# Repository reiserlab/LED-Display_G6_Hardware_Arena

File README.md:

## LED Display G6 Hardware Arena

This repository is part of <https://reiserlab.github.io/Modular-LED-Display/>. It contains the KiCad design files and production files for the Generation 6 arena hardware.

### Overview

The arena PCB serves as the backplane for a Generation 6 Modular LED Display. It supports up to 10 LED panel boards arranged in a circle to form a cylindrical structure. The board is driven by a Teensy 4.1 MCU and receives updates via Ethernet.

The first large production run was version 1.1.7, ordered on 2026-04-28.

## Development and License

The original design was created by Will Dickson of [IORodeo](https://iorodeo.com) for the [Reiser Lab](https://janelia.org/lab/reiser-lab) at [Janelia | HHMI](https://www.janelia.org/). See `LICENSE`.

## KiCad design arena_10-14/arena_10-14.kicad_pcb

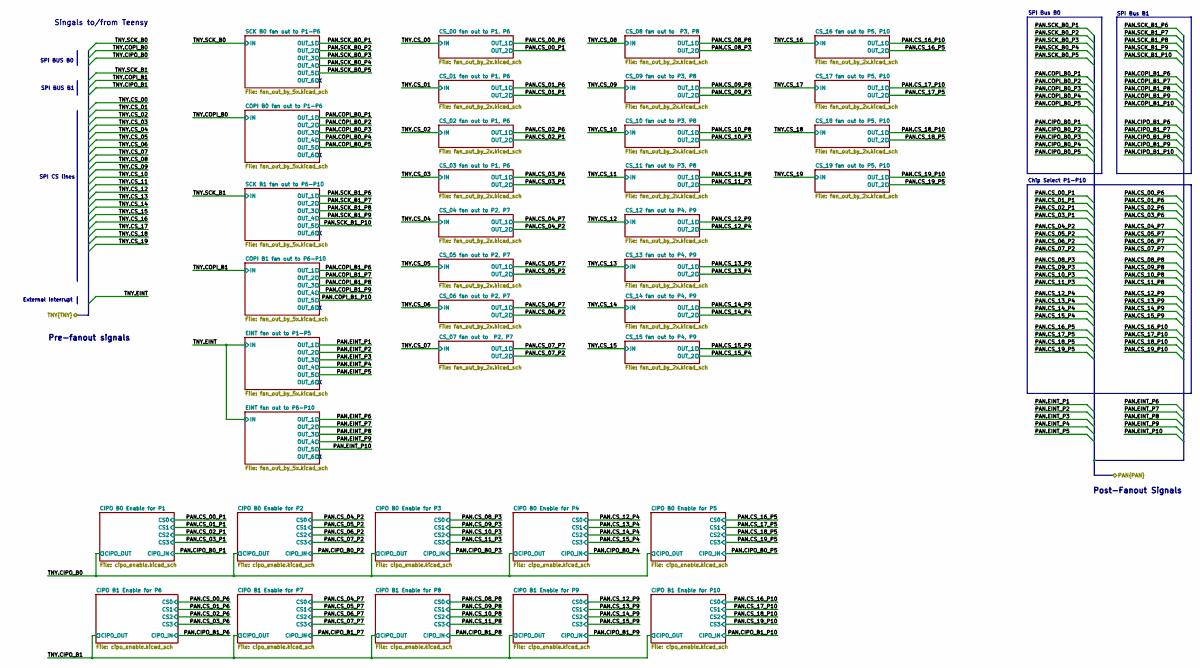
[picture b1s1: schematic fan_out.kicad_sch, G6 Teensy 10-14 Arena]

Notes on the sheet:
Chip Select P1-P10
Pre-fanout signals
SPI BUS B0
SPI BUS B1
External Interrupt
Post-Fanout Signals
SPI Bus B0
Singals to/from Teensy
SPI Bus B1
SPI CS lines

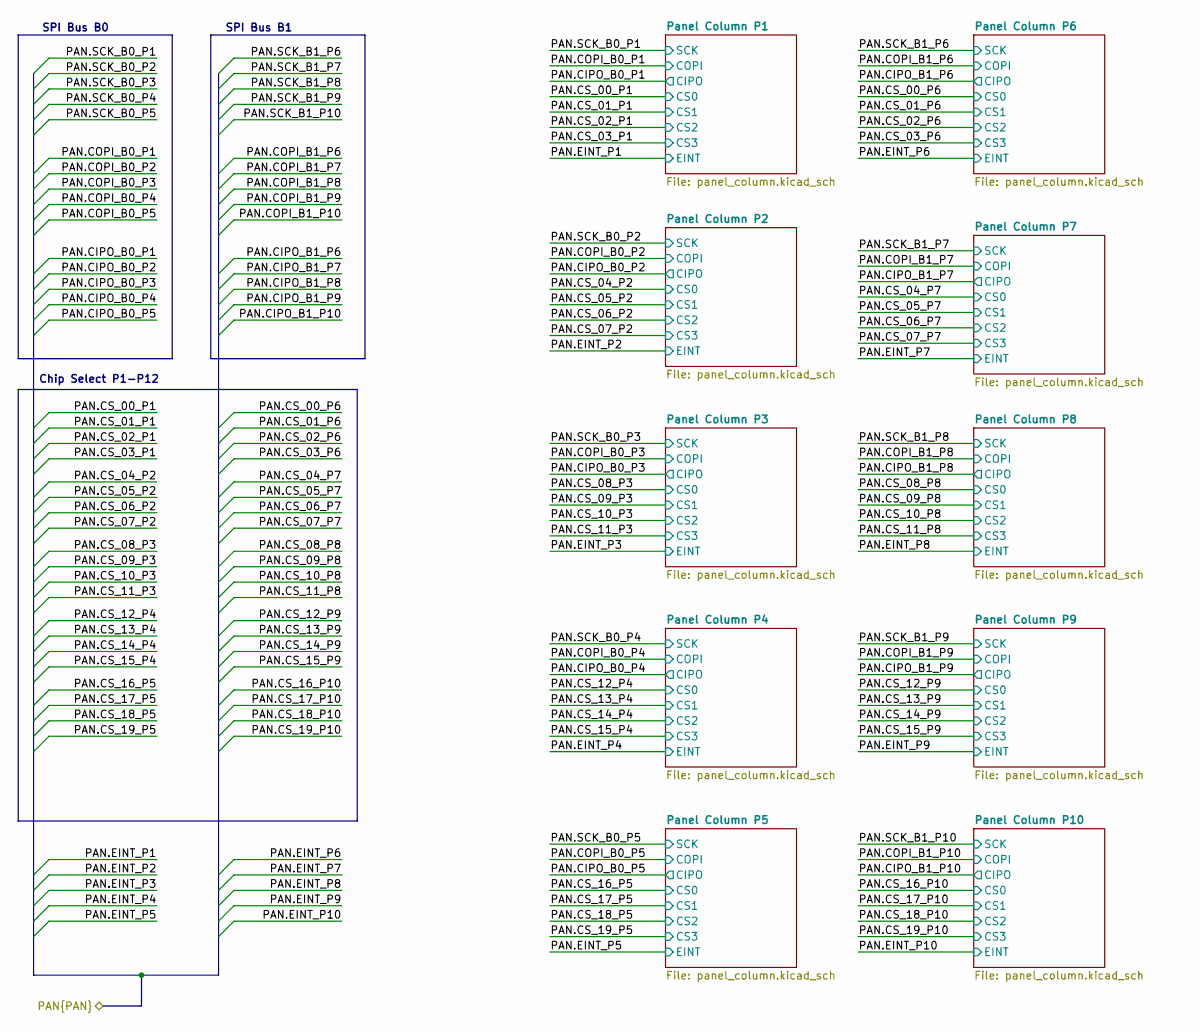
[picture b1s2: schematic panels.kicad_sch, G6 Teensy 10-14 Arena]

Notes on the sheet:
SPI Bus B1
Chip Select P1-P12
SPI Bus B0

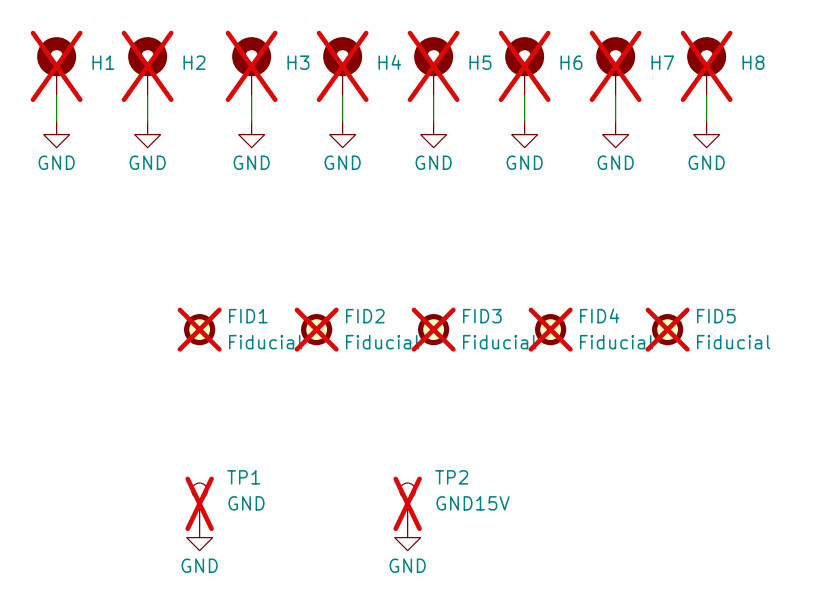
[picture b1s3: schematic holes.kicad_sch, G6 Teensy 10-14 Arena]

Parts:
FID1, FID2, FID3, FID4, FID5: Fiducial; Fiducial_0.5mm_Mask1mm; not fitted
H1, H2, H3, H4, H8: MountingHole_Pad; MountingHole_6.5mm_Pad_Via; not fitted
H5, H6, H7: MountingHole_Pad; MountingHole_6.5mm_Pad_TopBottom; not fitted
TP1: GND; TestPoint_Pad_D1.5mm; not fitted
TP2: GND15V; TestPoint_Pad_D1.5mm; not fitted

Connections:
GND: H1.1 (1_1), H2.1 (1_1), H3.1 (1_1), H4.1 (1_1), H5.1 (1_1), H6.1 (1_1), H7.1 (1_1), H8.1 (1_1), TP1.1 (1_1), TP2.1 (1_1); also elsewhere on the board

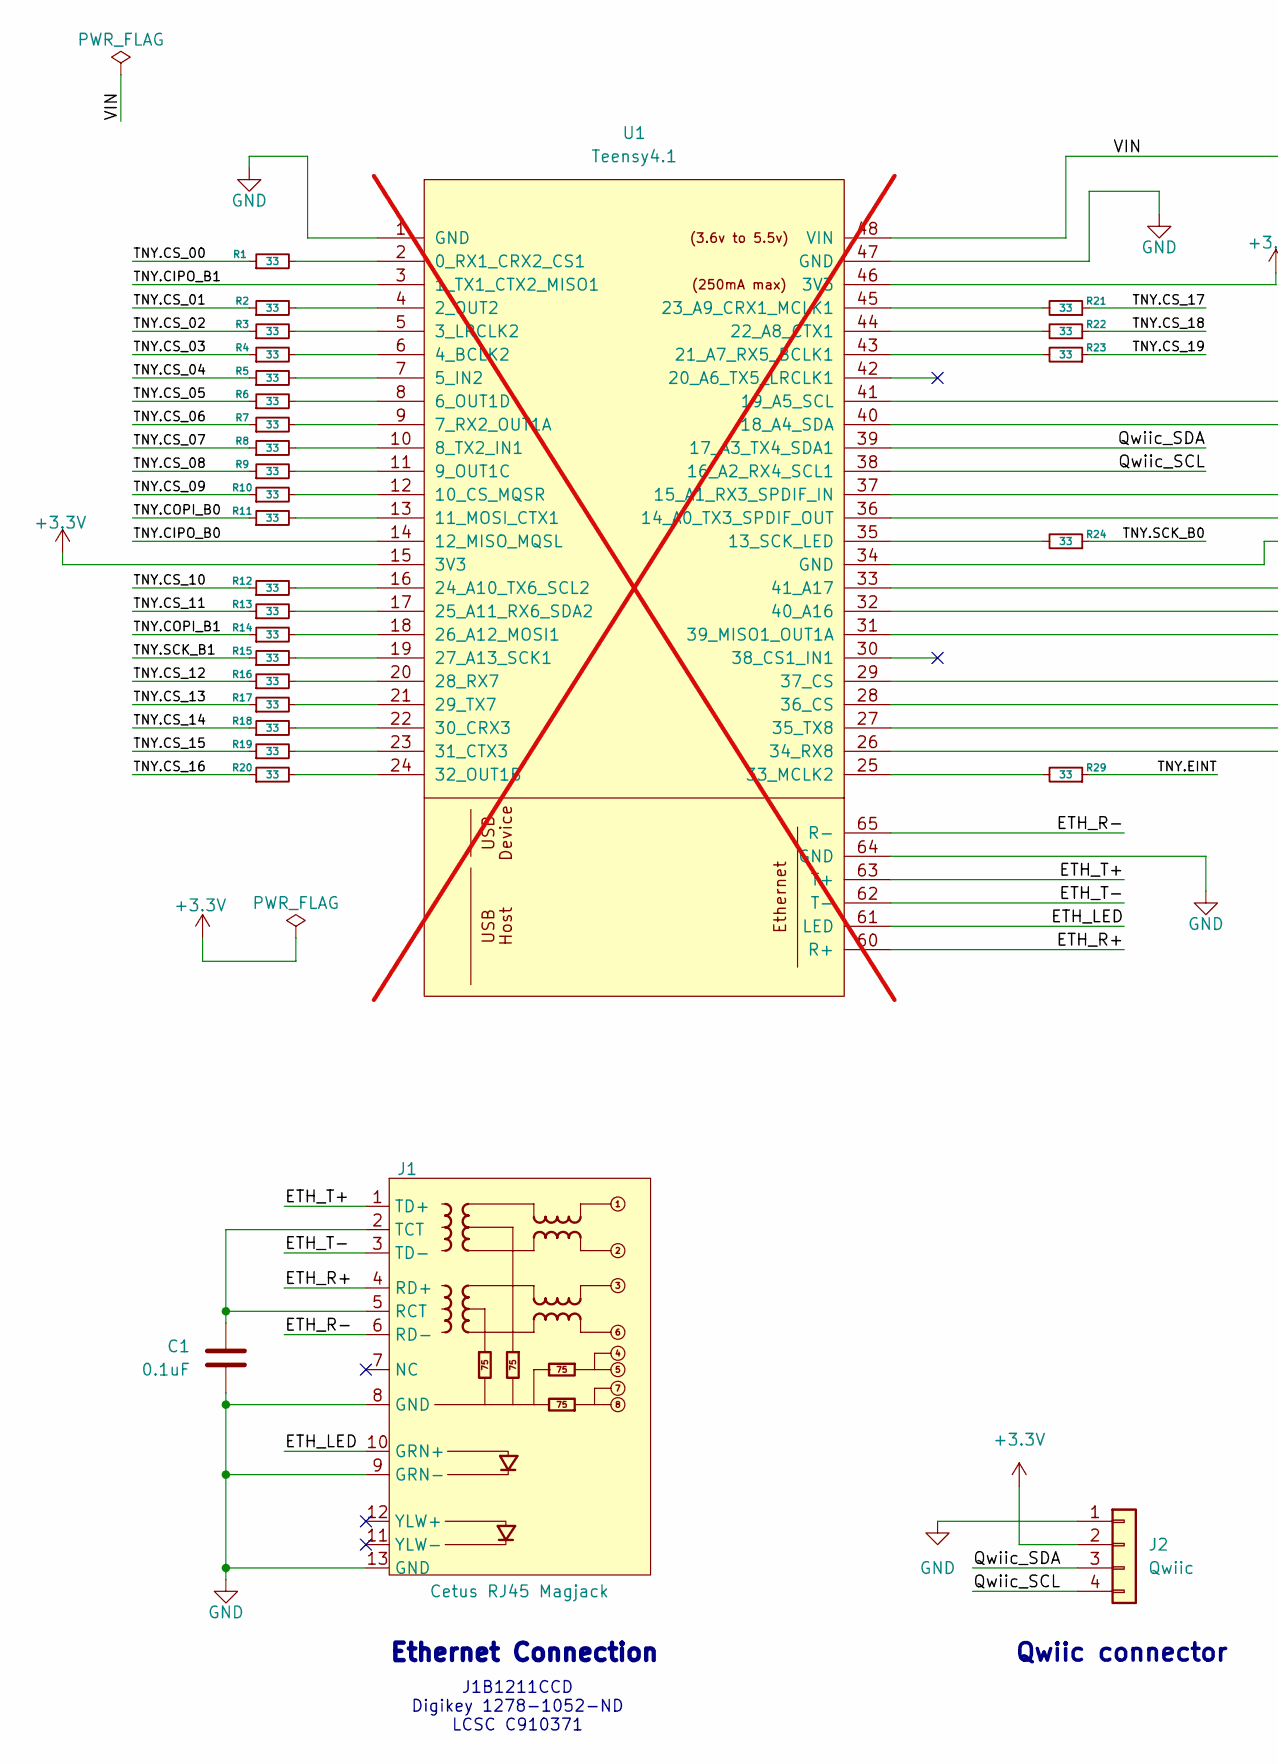
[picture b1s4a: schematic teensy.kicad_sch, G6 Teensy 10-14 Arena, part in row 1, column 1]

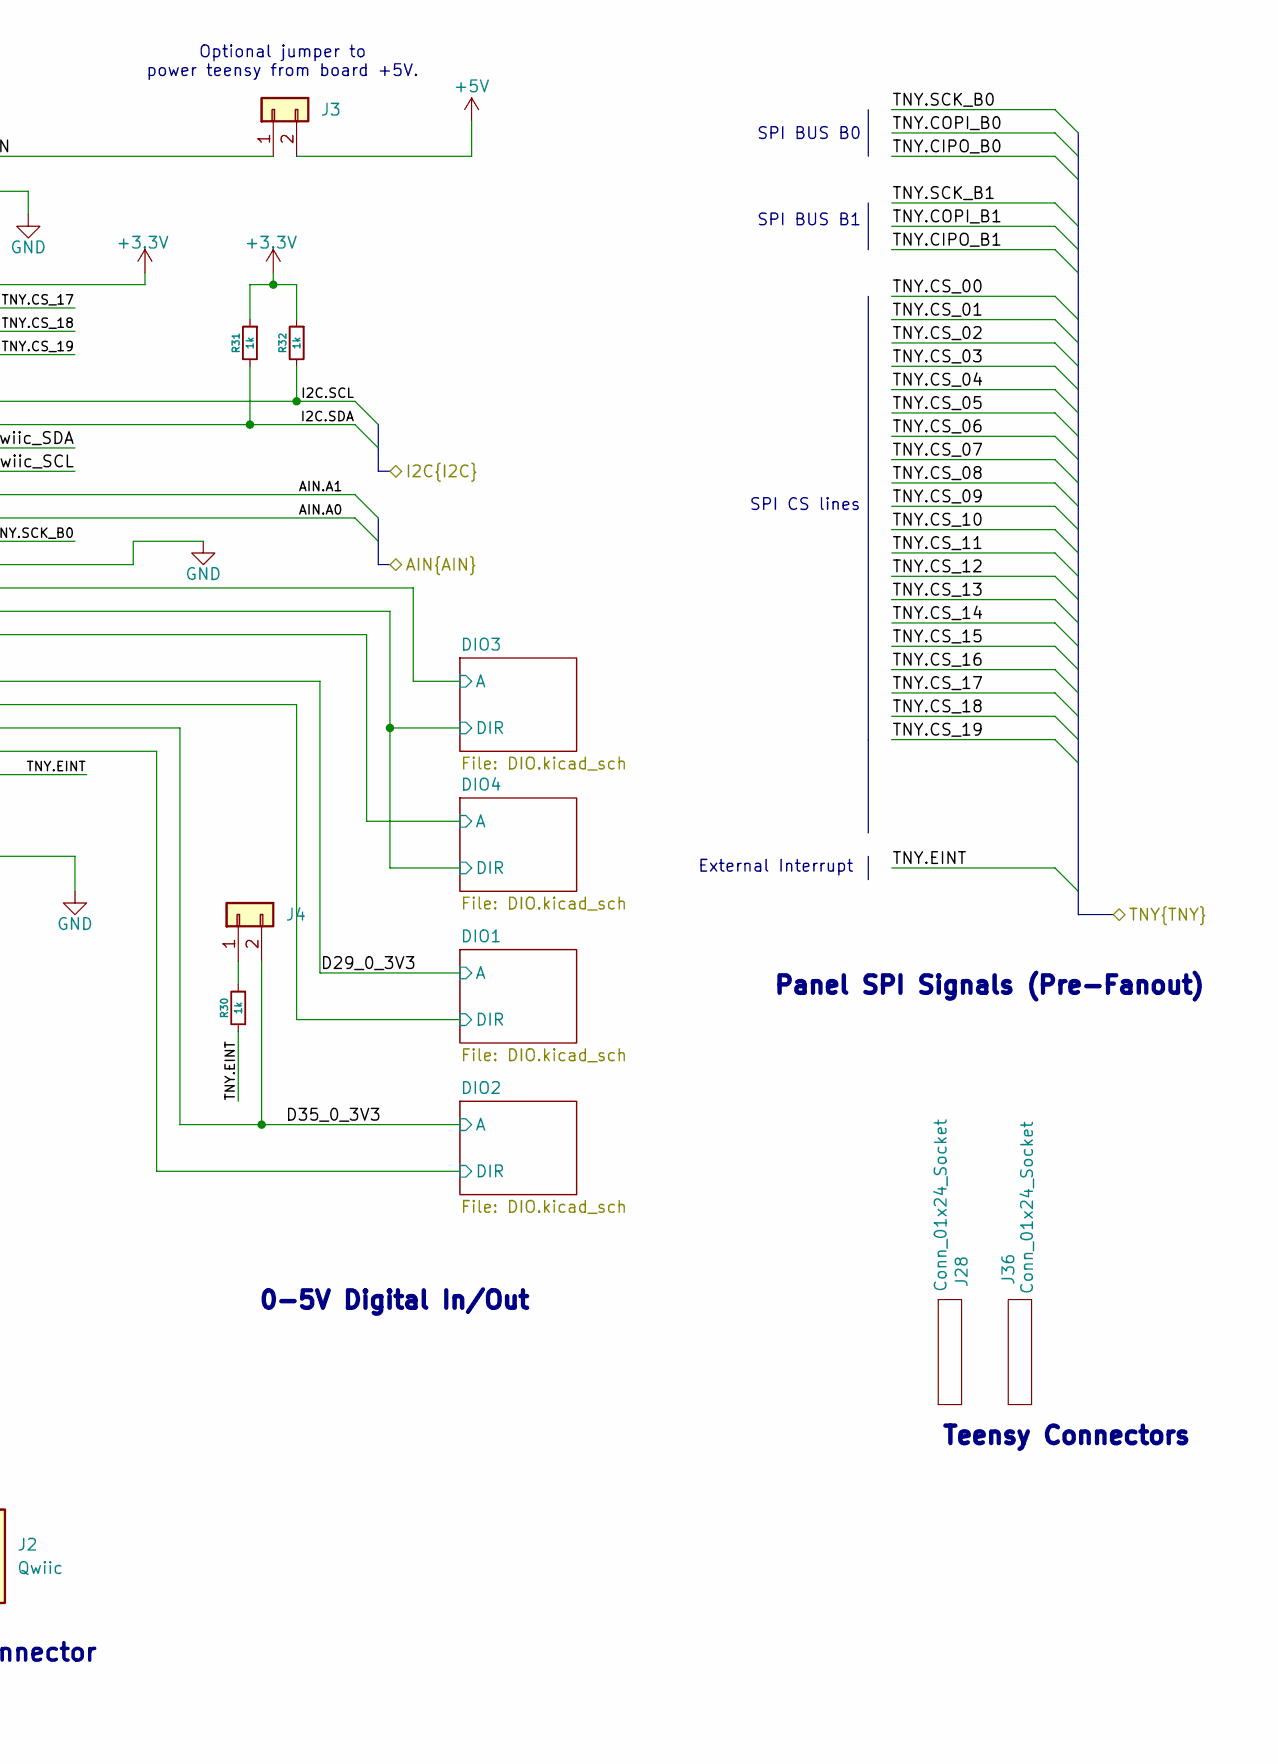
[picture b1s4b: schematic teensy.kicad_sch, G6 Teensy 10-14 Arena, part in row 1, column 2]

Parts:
C1: 0.1uF; C_0402_1005Metric; LCSC Part # C1525
J1: Cetus RJ45 Magjack; RJ45_Cetus_J1B1211CCD_Horizontal; LCSC Part # C910371
J2: Qwiic; JST_SH_SM04B-SRSS-TB_1x04-1MP_P1.00mm_Horizontal; MPN SM04B-SRSS-TB; DigiKey PN 455-SM04B-SRSS-TBTR-ND
J3, J4: Conn_01x02; PinHeader_1x02_P2.54mm_Vertical; LCSC Part # C124375
J28, J36: Conn_01x24_Socket; PinSocket_1x24_P2.54mm_Vertical; LCSC Part # C41376163
R1, R2, R3, R4, R5, R6, R7, R8, R9, R10, R11, R12, R13, R14, R15, R16, R17, R18, R19, R20, R21, R22, R23, R24, R29: 33; R_0402_1005Metric; LCSC Part # C25105
R30, R31, R32: 1k; R_0402_1005Metric; LCSC Part # C11702
U1: Teensy4.1; Teensy41_ethernet_only; not fitted

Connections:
+3.3V: J2.2, R31.1, R32.1, U1.15 (3V3), U1.46 (3V3); also elsewhere on the board
+5V: J3.2; also elsewhere on the board
/Analog IO/AIN.A0: U1.36 (14_A0_TX3_SPDIF_OUT); also elsewhere on the board
/Analog IO/AIN.A1: U1.37 (15_A1_RX3_SPDIF_IN); also elsewhere on the board
/Analog IO/I2C.SCL: R32.2, U1.41 (19_A5_SCL); also elsewhere on the board
/Analog IO/I2C.SDA: R31.2, U1.40 (18_A4_SDA); also elsewhere on the board
/Fan Out/TNY.CIPO_B0: U1.14 (12_MISO_MQSL); also elsewhere on the board
/Fan Out/TNY.CIPO_B1: U1.3 (1_TX1_CTX2_MISO1); also elsewhere on the board
/Fan Out/TNY.COPI_B0: R11.1; also elsewhere on the board
/Fan Out/TNY.COPI_B1: R14.1; also elsewhere on the board
/Fan Out/TNY.CS_00: R1.1; also elsewhere on the board
/Fan Out/TNY.CS_01: R2.1; also elsewhere on the board
/Fan Out/TNY.CS_02: R3.1; also elsewhere on the board
/Fan Out/TNY.CS_03: R4.1; also elsewhere on the board
/Fan Out/TNY.CS_04: R5.1; also elsewhere on the board
/Fan Out/TNY.CS_05: R6.1; also elsewhere on the board
/Fan Out/TNY.CS_06: R7.1; also elsewhere on the board
/Fan Out/TNY.CS_07: R8.1; also elsewhere on the board
/Fan Out/TNY.CS_08: R9.1; also elsewhere on the board
/Fan Out/TNY.CS_09: R10.1; also elsewhere on the board
/Fan Out/TNY.CS_10: R12.1; also elsewhere on the board
/Fan Out/TNY.CS_11: R13.1; also elsewhere on the board
/Fan Out/TNY.CS_12: R16.1; also elsewhere on the board
/Fan Out/TNY.CS_13: R17.1; also elsewhere on the board
/Fan Out/TNY.CS_14: R18.1; also elsewhere on the board
/Fan Out/TNY.CS_15: R19.1; also elsewhere on the board
/Fan Out/TNY.CS_16: R20.1; also elsewhere on the board
/Fan Out/TNY.CS_17: R21.1; also elsewhere on the board
/Fan Out/TNY.CS_18: R22.1; also elsewhere on the board
/Fan Out/TNY.CS_19: R23.1; also elsewhere on the board
/Fan Out/TNY.EINT: R29.1, R30.2; also elsewhere on the board
/Fan Out/TNY.SCK_B0: R24.1; also elsewhere on the board
/Fan Out/TNY.SCK_B1: R15.1; also elsewhere on the board
/Teensy/D29_0_3V3: U1.29 (37_CS); also elsewhere on the board
/Teensy/D35_0_3V3: J4.2, U1.27 (35_TX8); also elsewhere on the board
/Teensy/DIO1/DIR: U1.28 (36_CS); also elsewhere on the board
/Teensy/DIO2/DIR: U1.26 (34_RX8); also elsewhere on the board
/Teensy/DIO3/A: U1.33 (41_A17); also elsewhere on the board
/Teensy/DIO3/DIR: U1.32 (40_A16); also elsewhere on the board
/Teensy/DIO4/A: U1.31 (39_MISO1_OUT1A); also elsewhere on the board
/Teensy/ETH_LED: J1.10 (GRN+), U1.61 (LED)
/Teensy/ETH_R+: J1.4 (RD+), U1.60 (R+)
/Teensy/ETH_R-: J1.6 (RD-), U1.65 (R-)
/Teensy/ETH_T+: J1.1 (TD+), U1.63 (T+)
/Teensy/ETH_T-: J1.3 (TD-), U1.62 (T-)
/Teensy/Qwiic_SCL: J2.4, U1.38 (16_A2_RX4_SCL1)
/Teensy/Qwiic_SDA: J2.3, U1.39 (17_A3_TX4_SDA1)
/Teensy/VIN: J3.1, U1.48 (VIN)
GND: C1.2, J1.8 (GND), J1.9 (GRN-), J1.13 (GND), J2.1, J2.MP (MountPin), U1.1 (GND), U1.34 (GND), U1.47 (GND), U1.64 (GND); also elsewhere on the board
unnamed: C1.1, J1.2 (TCT), J1.5 (RCT)
unnamed: J4.1, R30.1
unnamed: R1.2, U1.2 (0_RX1_CRX2_CS1)
unnamed: R2.2, U1.4 (2_OUT2)
unnamed: R3.2, U1.5 (3_LRCLK2)
unnamed: R4.2, U1.6 (4_BCLK2)
unnamed: R5.2, U1.7 (5_IN2)
unnamed: R6.2, U1.8 (6_OUT1D)
unnamed: R7.2, U1.9 (7_RX2_OUT1A)
unnamed: R8.2, U1.10 (8_TX2_IN1)
unnamed: R9.2, U1.11 (9_OUT1C)
unnamed: R10.2, U1.12 (10_CS_MQSR)
unnamed: R11.2, U1.13 (11_MOSI_CTX1)
unnamed: R24.2, U1.35 (13_SCK_LED)
unnamed: R23.2, U1.43 (21_A7_RX5_BCLK1)
unnamed: R22.2, U1.44 (22_A8_CTX1)
unnamed: R21.2, U1.45 (23_A9_CRX1_MCLK1)
unnamed: R12.2, U1.16 (24_A10_TX6_SCL2)
unnamed: R13.2, U1.17 (25_A11_RX6_SDA2)
unnamed: R14.2, U1.18 (26_A12_MOSI1)
unnamed: R15.2, U1.19 (27_A13_SCK1)
unnamed: R16.2, U1.20 (28_RX7)
unnamed: R17.2, U1.21 (29_TX7)
unnamed: R18.2, U1.22 (30_CRX3)
unnamed: R19.2, U1.23 (31_CTX3)
unnamed: R20.2, U1.24 (32_OUT1B)
unnamed: R29.2, U1.25 (33_MCLK2)

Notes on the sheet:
Panel SPI Signals (Pre-Fanout)
Optional jumper to power teensy from board +5V.
J1B1211CCD Digikey 1278-1052-ND LCSC C910371
SPI BUS B0
Teensy Connectors
0-5V Digital In/Out
Qwiic connector
External Interrupt
SPI BUS B1
Ethernet Connection
SPI CS lines

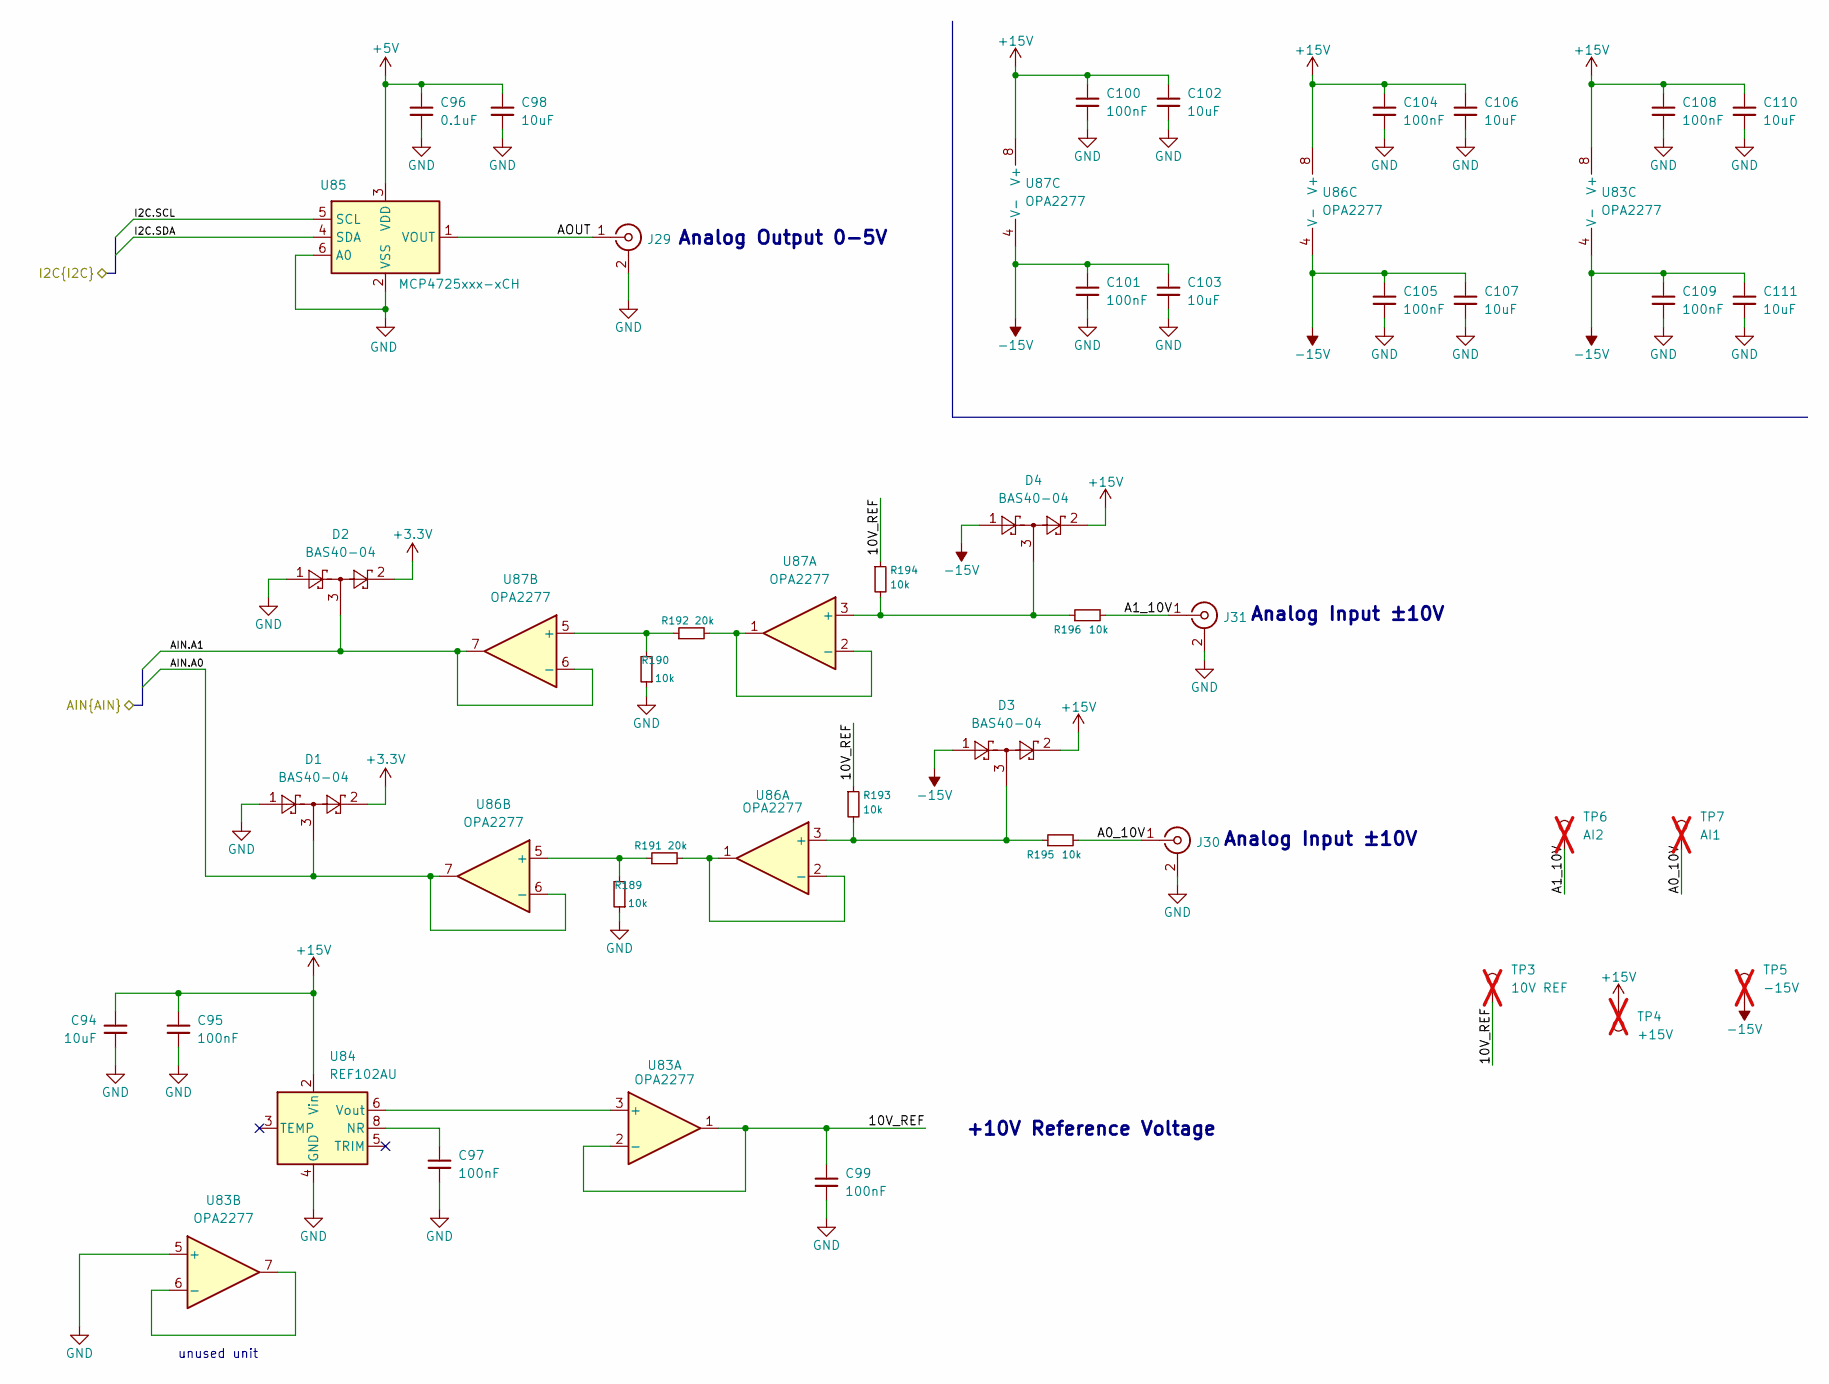
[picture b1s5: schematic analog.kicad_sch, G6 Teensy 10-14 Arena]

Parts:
C94, C98, C102, C103, C106, C107, C110, C111: 10uF; C_1206_3216Metric; LCSC Part # C89632
C95, C97, C99, C100, C101, C104, C105, C108, C109: 100nF; C_0402_1005Metric; LCSC Part # C307331
C96: 0.1uF; C_0402_1005Metric; LCSC Part # C1525
D1, D2, D3, D4: BAS40-04; SOT-23; LCSC Part # C7502688
J29, J30, J31: Conn_Coaxial; BNC_HenryTech_HL-BNC_KHDA; LCSC Part # C19712152
R189, R190, R193, R194, R195, R196: 10k; R_0402_1005Metric; LCSC Part # C190095
R191, R192: 20k; R_0402_1005Metric; LCSC Part # C705630
TP3: 10V REF; TestPoint_Pad_D1.5mm; not fitted
TP4: +15V; TestPoint_Pad_D1.5mm; not fitted
TP5: -15V; TestPoint_Pad_D1.5mm; not fitted
TP6: AI2; TestPoint_Pad_D1.5mm; not fitted
TP7: AI1; TestPoint_Pad_D1.5mm; not fitted
U83, U86, U87: OPA2277; SOIC-8_3.9x4.9mm_P1.27mm; LCSC Part # C24460
U84: REF102AU; SOIC-8_3.9x4.9mm_P1.27mm; LCSC Part # C81460
U85: MCP4725xxx-xCH; SOT-23-6; LCSC Part # C144198

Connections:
+3.3V: D1.2, D2.2; also elsewhere on the board
+5V: C96.1, C98.1, U85.3 (VDD); also elsewhere on the board
+15V: C94.1, C95.1, C100.1, C102.1, C104.1, C106.1, C108.1, C110.1, D3.2, D4.2, TP4.1 (1_1), U83.8 (V+), U84.2 (Vin), U86.8 (V+), U87.8 (V+); also elsewhere on the board
-15V: C101.1, C103.1, C105.1, C107.1, C109.1, C111.1, D3.1, D4.1, TP5.1 (1_1), U83.4 (V-), U86.4 (V-), U87.4 (V-); also elsewhere on the board
/Analog IO/10V_REF: C99.1, R193.1, R194.1, TP3.1 (1_1), U83.1, U83.2 (-)
/Analog IO/A0_10V: J30.1 (In), R195.2, TP7.1 (1_1)
/Analog IO/A1_10V: J31.1 (In), R196.2, TP6.1 (1_1)
/Analog IO/AIN.A0: D1.3, U86.6 (-), U86.7; also elsewhere on the board
/Analog IO/AIN.A1: D2.3, U87.6 (-), U87.7; also elsewhere on the board
/Analog IO/AOUT: J29.1 (In), U85.1 (VOUT)
/Analog IO/I2C.SCL: U85.5 (SCL); also elsewhere on the board
/Analog IO/I2C.SDA: U85.4 (SDA); also elsewhere on the board
GND: C94.2, C95.2, C96.2, C97.2, C98.2, C99.2, C100.2, C101.2, C102.2, C103.2, C104.2, C105.2, C106.2, C107.2, C108.2, C109.2, C110.2, C111.2, D1.1, D2.1, J29.2 (Ext), J30.2 (Ext), J31.2 (Ext), R189.1, R190.1, U83.5 (+), U84.4 (GND), U85.2 (VSS), U85.6 (A0); also elsewhere on the board
unnamed: U83.3 (+), U84.6 (Vout)
unnamed: U83.6 (-), U83.7
unnamed: C97.1, U84.8 (NR)
unnamed: D3.3, R193.2, R195.1, U86.3 (+)
unnamed: R191.2, U86.1, U86.2 (-)
unnamed: R189.2, R191.1, U86.5 (+)
unnamed: D4.3, R194.2, R196.1, U87.3 (+)
unnamed: R192.2, U87.1, U87.2 (-)
unnamed: R190.2, R192.1, U87.5 (+)

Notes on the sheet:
unused unit
+10V Reference Voltage
Analog Output 0-5V
Analog Input ±10V

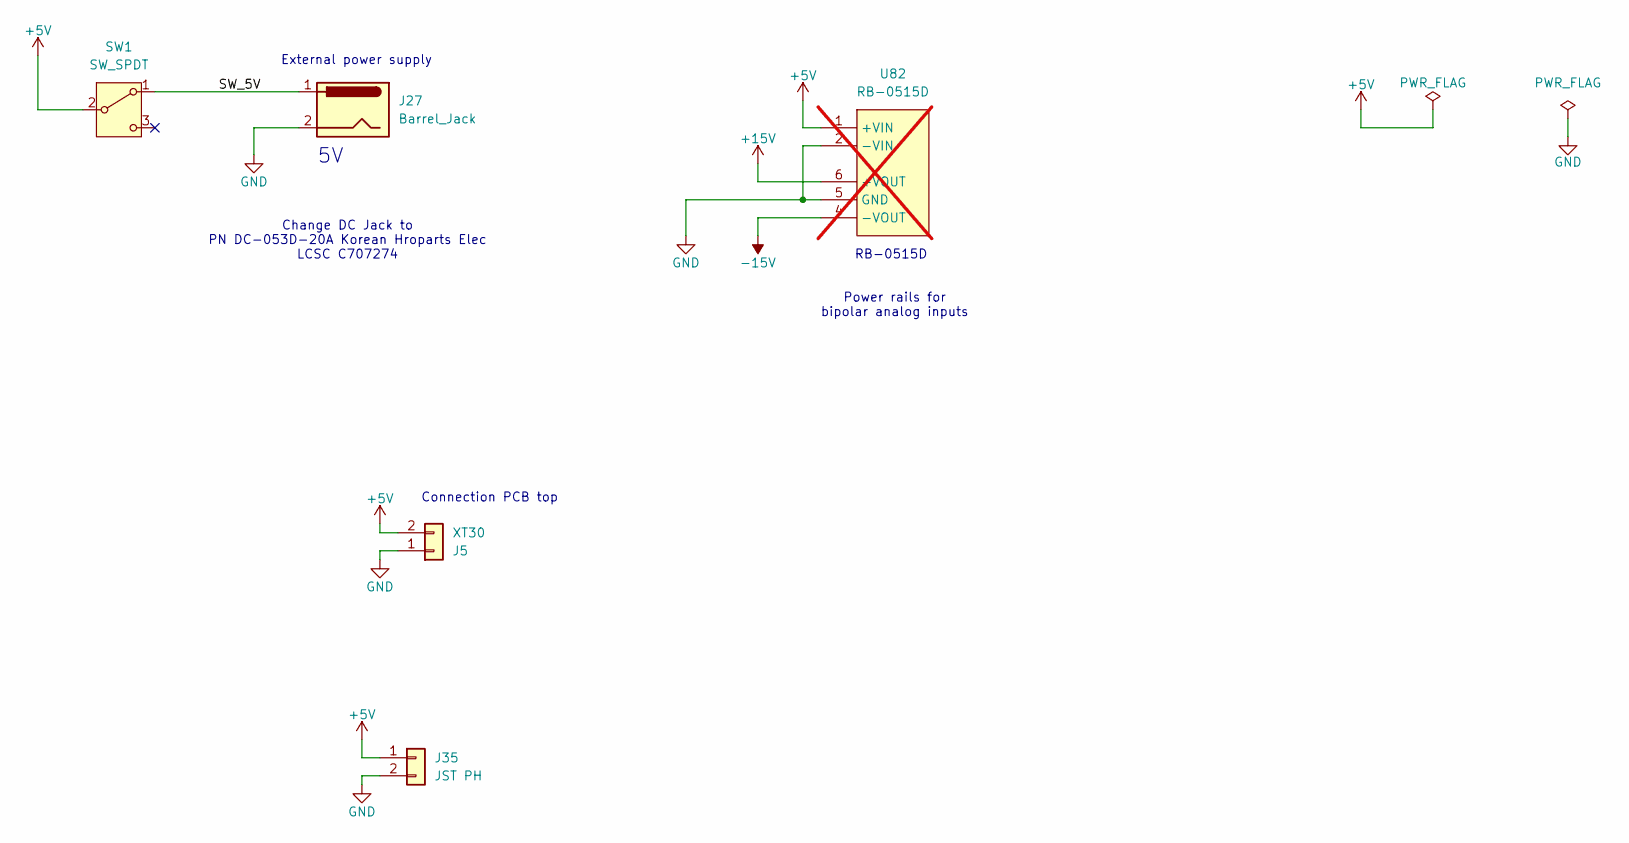
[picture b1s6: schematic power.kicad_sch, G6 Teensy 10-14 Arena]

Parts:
J5: XT30; AMASS_XT30UPB-F_1x02_P5.0mm_Vertical; LCSC Part # C108769
J27: Barrel_Jack; DC-053D-20A; LCSC Part # C707274
J35: JST PH; JST_PH_B2B-PH-K_1x02_P2.00mm_Vertical; LCSC Part # C594142
SW1: SW_SPDT; slide_switch; LCSC Part # C2884789
U82: RB-0515D; RB-XXYYYD; not fitted

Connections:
+5V: J5.2, J35.1, SW1.2 (B), U82.1 (+VIN); also elsewhere on the board
+15V: U82.6 (+VOUT); also elsewhere on the board
-15V: U82.4 (-VOUT); also elsewhere on the board
/Power/SW_5V: J27.1, SW1.1 (A)
GND: J5.1, J27.2, J35.2, U82.2 (-VIN), U82.5 (GND); also elsewhere on the board

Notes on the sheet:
Change DC Jack to PN DC-053D-20A Korean Hroparts Elec LCSC C707274
External power supply
Power rails for bipolar analog inputs
Connection PCB top
RB-0515D

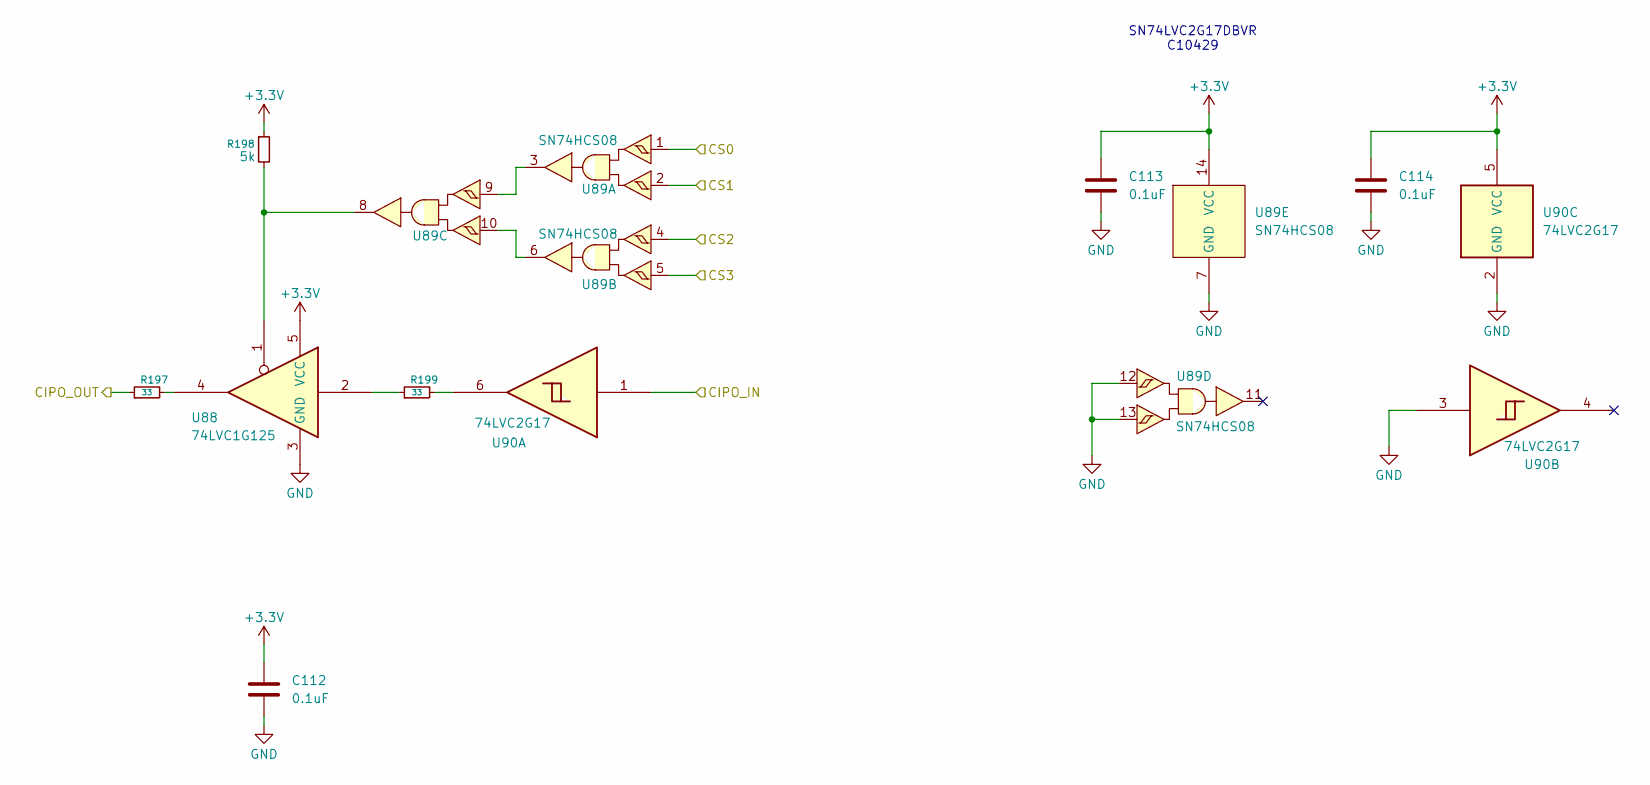
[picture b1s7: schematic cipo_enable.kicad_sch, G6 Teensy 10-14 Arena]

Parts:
C112, C113, C114: 0.1uF; C_0402_1005Metric; LCSC Part # C1525
R197, R199: 33; R_0402_1005Metric; LCSC Part # C25105
R198: 5k; R_0402_1005Metric; LCSC Part # C5948099
U88: 74LVC1G125; SOT-23-5; LCSC Part # C7394017
U89: SN74HCS08; SOIC-14_3.9x8.7mm_P1.27mm; LCSC Part # C2868021
U90: 74LVC2G17; SOT-23-6; LCSC Part # C7394037

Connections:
+3.3V: C112.1, C113.1, C114.1, R198.1, U88.5 (VCC), U89.14 (VCC), U90.5 (VCC); also elsewhere on the board
/Fan Out/PAN.CIPO_B0_P1: U90.1; also elsewhere on the board
/Fan Out/PAN.CS_00_P1: U89.1; also elsewhere on the board
/Fan Out/PAN.CS_01_P1: U89.2; also elsewhere on the board
/Fan Out/PAN.CS_02_P1: U89.4; also elsewhere on the board
/Fan Out/PAN.CS_03_P1: U89.5; also elsewhere on the board
/Fan Out/TNY.CIPO_B0: R197.1; also elsewhere on the board
GND: C112.2, C113.2, C114.2, U88.3 (GND), U89.7 (GND), U89.12, U89.13, U90.2 (GND), U90.3; also elsewhere on the board
unnamed: R197.2, U88.4
unnamed: R198.2, U88.1, U89.8
unnamed: R199.1, U88.2
unnamed: R199.2, U90.6
unnamed: U89.3, U89.9
unnamed: U89.6, U89.10

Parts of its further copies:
C115, C116, C117, C118, C119, C120, C121, C122, C123, C124, C125, C126, C127, C128, C129, C130, C131, C132, C133, C134, C135, C136, C137, C138, C146, C147, C148: 0.1uF; C_0402_1005Metric; LCSC Part # C1525
R200, R202, R203, R205, R206, R208, R209, R211, R212, R214, R215, R217, R218, R220, R221, R223, R235, R237: 33; R_0402_1005Metric; LCSC Part # C25105
R201, R204, R207, R210, R213, R216, R219, R222, R236: 5k; R_0402_1005Metric; LCSC Part # C5948099
U91, U94, U97, U100, U103, U106, U109, U112, U122: 74LVC1G125; SOT-23-5; LCSC Part # C7394017
U92, U95, U98, U101, U104, U107, U110, U113, U123: SN74HCS08; SOIC-14_3.9x8.7mm_P1.27mm; LCSC Part # C2868021
U93, U96, U99, U102, U105, U108, U111, U114, U124: 74LVC2G17; SOT-23-6; LCSC Part # C7394037

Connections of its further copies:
+3.3V: C115.1, C116.1, C117.1, C118.1, C119.1, C120.1, C121.1, C122.1, C123.1, C124.1, C125.1, C126.1, C127.1, C128.1, C129.1, C130.1, C131.1, C132.1, C133.1, C134.1, C135.1, C136.1, C137.1, C138.1, C146.1, C147.1, C148.1, R201.1, R204.1, R207.1, R210.1, R213.1, R216.1, R219.1, R222.1, R236.1, U91.5 (VCC), U92.14 (VCC), U93.5 (VCC), U94.5 (VCC), U95.14 (VCC), U96.5 (VCC), U97.5 (VCC), U98.14 (VCC), U99.5 (VCC), U100.5 (VCC), U101.14 (VCC), U102.5 (VCC), U103.5 (VCC), U104.14 (VCC), U105.5 (VCC), U106.5 (VCC), U107.14 (VCC), U108.5 (VCC), U109.5 (VCC), U110.14 (VCC), U111.5 (VCC), U112.5 (VCC), U113.14 (VCC), U114.5 (VCC), U122.5 (VCC), U123.14 (VCC), U124.5 (VCC); also elsewhere on the board
/Fan Out/PAN.CIPO_B0_P2: U93.1; also elsewhere on the board
/Fan Out/PAN.CIPO_B0_P3: U96.1; also elsewhere on the board
/Fan Out/PAN.CIPO_B0_P4: U99.1; also elsewhere on the board
/Fan Out/PAN.CIPO_B0_P5: U102.1; also elsewhere on the board
/Fan Out/PAN.CIPO_B1_P6: U124.1; also elsewhere on the board
/Fan Out/PAN.CIPO_B1_P7: U105.1; also elsewhere on the board
/Fan Out/PAN.CIPO_B1_P8: U108.1; also elsewhere on the board
/Fan Out/PAN.CIPO_B1_P9: U111.1; also elsewhere on the board
/Fan Out/PAN.CIPO_B1_P10: U114.1; also elsewhere on the board
/Fan Out/PAN.CS_00_P6: U123.1; also elsewhere on the board
/Fan Out/PAN.CS_01_P6: U123.2; also elsewhere on the board
/Fan Out/PAN.CS_02_P6: U123.4; also elsewhere on the board
/Fan Out/PAN.CS_03_P6: U123.5; also elsewhere on the board
/Fan Out/PAN.CS_04_P2: U92.1; also elsewhere on the board
/Fan Out/PAN.CS_04_P7: U104.1; also elsewhere on the board
/Fan Out/PAN.CS_05_P2: U92.2; also elsewhere on the board
/Fan Out/PAN.CS_05_P7: U104.2; also elsewhere on the board
/Fan Out/PAN.CS_06_P2: U92.4; also elsewhere on the board
/Fan Out/PAN.CS_06_P7: U104.4; also elsewhere on the board
/Fan Out/PAN.CS_07_P2: U92.5; also elsewhere on the board
/Fan Out/PAN.CS_07_P7: U104.5; also elsewhere on the board
/Fan Out/PAN.CS_08_P3: U95.1; also elsewhere on the board
/Fan Out/PAN.CS_08_P8: U107.1; also elsewhere on the board
/Fan Out/PAN.CS_09_P3: U95.2; also elsewhere on the board
/Fan Out/PAN.CS_09_P8: U107.2; also elsewhere on the board
/Fan Out/PAN.CS_10_P3: U95.4; also elsewhere on the board
/Fan Out/PAN.CS_10_P8: U107.4; also elsewhere on the board
/Fan Out/PAN.CS_11_P3: U95.5; also elsewhere on the board
/Fan Out/PAN.CS_11_P8: U107.5; also elsewhere on the board
/Fan Out/PAN.CS_12_P4: U98.1; also elsewhere on the board
/Fan Out/PAN.CS_12_P9: U110.1; also elsewhere on the board
/Fan Out/PAN.CS_13_P4: U98.2; also elsewhere on the board
/Fan Out/PAN.CS_13_P9: U110.2; also elsewhere on the board
/Fan Out/PAN.CS_14_P4: U98.4; also elsewhere on the board
/Fan Out/PAN.CS_14_P9: U110.4; also elsewhere on the board
/Fan Out/PAN.CS_15_P4: U98.5; also elsewhere on the board
/Fan Out/PAN.CS_15_P9: U110.5; also elsewhere on the board
/Fan Out/PAN.CS_16_P5: U101.1; also elsewhere on the board
/Fan Out/PAN.CS_16_P10: U113.1; also elsewhere on the board
/Fan Out/PAN.CS_17_P5: U101.2; also elsewhere on the board
/Fan Out/PAN.CS_17_P10: U113.2; also elsewhere on the board
/Fan Out/PAN.CS_18_P5: U101.4; also elsewhere on the board
/Fan Out/PAN.CS_18_P10: U113.4; also elsewhere on the board
/Fan Out/PAN.CS_19_P5: U101.5; also elsewhere on the board
/Fan Out/PAN.CS_19_P10: U113.5; also elsewhere on the board
/Fan Out/TNY.CIPO_B0: R200.1, R203.1, R206.1, R209.1; also elsewhere on the board
/Fan Out/TNY.CIPO_B1: R212.1, R215.1, R218.1, R221.1, R235.1; also elsewhere on the board
GND: C115.2, C116.2, C117.2, C118.2, C119.2, C120.2, C121.2, C122.2, C123.2, C124.2, C125.2, C126.2, C127.2, C128.2, C129.2, C130.2, C131.2, C132.2, C133.2, C134.2, C135.2, C136.2, C137.2, C138.2, C146.2, C147.2, C148.2, U91.3 (GND), U92.7 (GND), U92.12, U92.13, U93.2 (GND), U93.3, U94.3 (GND), U95.7 (GND), U95.12, U95.13, U96.2 (GND), U96.3, U97.3 (GND), U98.7 (GND), U98.12, U98.13, U99.2 (GND), U99.3, U100.3 (GND), U101.7 (GND), U101.12, U101.13, U102.2 (GND), U102.3, U103.3 (GND), U104.7 (GND), U104.12, U104.13, U105.2 (GND), U105.3, U106.3 (GND), U107.7 (GND), U107.12, U107.13, U108.2 (GND), U108.3, U109.3 (GND), U110.7 (GND), U110.12, U110.13, U111.2 (GND), U111.3, U112.3 (GND), U113.7 (GND), U113.12, U113.13, U114.2 (GND), U114.3, U122.3 (GND), U123.7 (GND), U123.12, U123.13, U124.2 (GND), U124.3; also elsewhere on the board
unnamed: R200.2, U91.4
unnamed: R201.2, U91.1, U92.8
unnamed: R202.1, U91.2
unnamed: R202.2, U93.6
unnamed: R203.2, U94.4
unnamed: R204.2, U94.1, U95.8
unnamed: R205.1, U94.2
unnamed: R205.2, U96.6
unnamed: R206.2, U97.4
unnamed: R207.2, U97.1, U98.8
unnamed: R208.1, U97.2
unnamed: R208.2, U99.6
unnamed: R209.2, U100.4
unnamed: R210.2, U100.1, U101.8
unnamed: R211.1, U100.2
unnamed: R211.2, U102.6
unnamed: R212.2, U103.4
unnamed: R213.2, U103.1, U104.8
unnamed: R214.1, U103.2
unnamed: R214.2, U105.6
unnamed: R215.2, U106.4
unnamed: R216.2, U106.1, U107.8
unnamed: R217.1, U106.2
unnamed: R217.2, U108.6
unnamed: R218.2, U109.4
unnamed: R219.2, U109.1, U110.8
unnamed: R220.1, U109.2
unnamed: R220.2, U111.6
unnamed: R221.2, U112.4
unnamed: R222.2, U112.1, U113.8
unnamed: R223.1, U112.2
unnamed: R223.2, U114.6
unnamed: R235.2, U122.4
unnamed: R236.2, U122.1, U123.8
unnamed: R237.1, U122.2
unnamed: R237.2, U124.6
unnamed: U92.3, U92.9
unnamed: U92.6, U92.10
unnamed: U95.3, U95.9
unnamed: U95.6, U95.10
unnamed: U98.3, U98.9
unnamed: U98.6, U98.10
unnamed: U101.3, U101.9
unnamed: U101.6, U101.10
unnamed: U104.3, U104.9
unnamed: U104.6, U104.10
unnamed: U107.3, U107.9
unnamed: U107.6, U107.10
unnamed: U110.3, U110.9
unnamed: U110.6, U110.10
unnamed: U113.3, U113.9
unnamed: U113.6, U113.10
unnamed: U123.3, U123.9
unnamed: U123.6, U123.10

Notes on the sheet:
SN74LVC2G17DBVR C10429
